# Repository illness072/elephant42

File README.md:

# elephant42 (🐘42)

## plates

|||
|--|--|
|dxf data in plates/|sandwitch mount with 6.5mm spacer|

## pcb

dependency on

  - https://github.com/foostan/kbd/tree/master/kicad-footprints/kbd.pretty

## cases

currently, not compatible with some switches.

## assembly

- [Build Guide (Japanese)](docs/build-guide.md)
- [Build Guide (English)](docs/build-guide-english.md)

## license?

Beerware!!

Come drink beer in Tokyo with me!! 🍺🍺🍺

## poor english?

Sorry, it's Google Translate.

# A small favor.

Could you generate a Gerber file from the origin/footprint branch and actually manufacture the PCB? 
We have implemented a fix for the footprint library link error and KiCAD6 support, but we have not yet been able to manufacture a PCB and test that it really works.
I would be most grateful if you could actually manufacture the PCB based on the footprint branch, check that it works, and report the results to me via Issue in this repository, my twitter, etc.
Thanks in advance.

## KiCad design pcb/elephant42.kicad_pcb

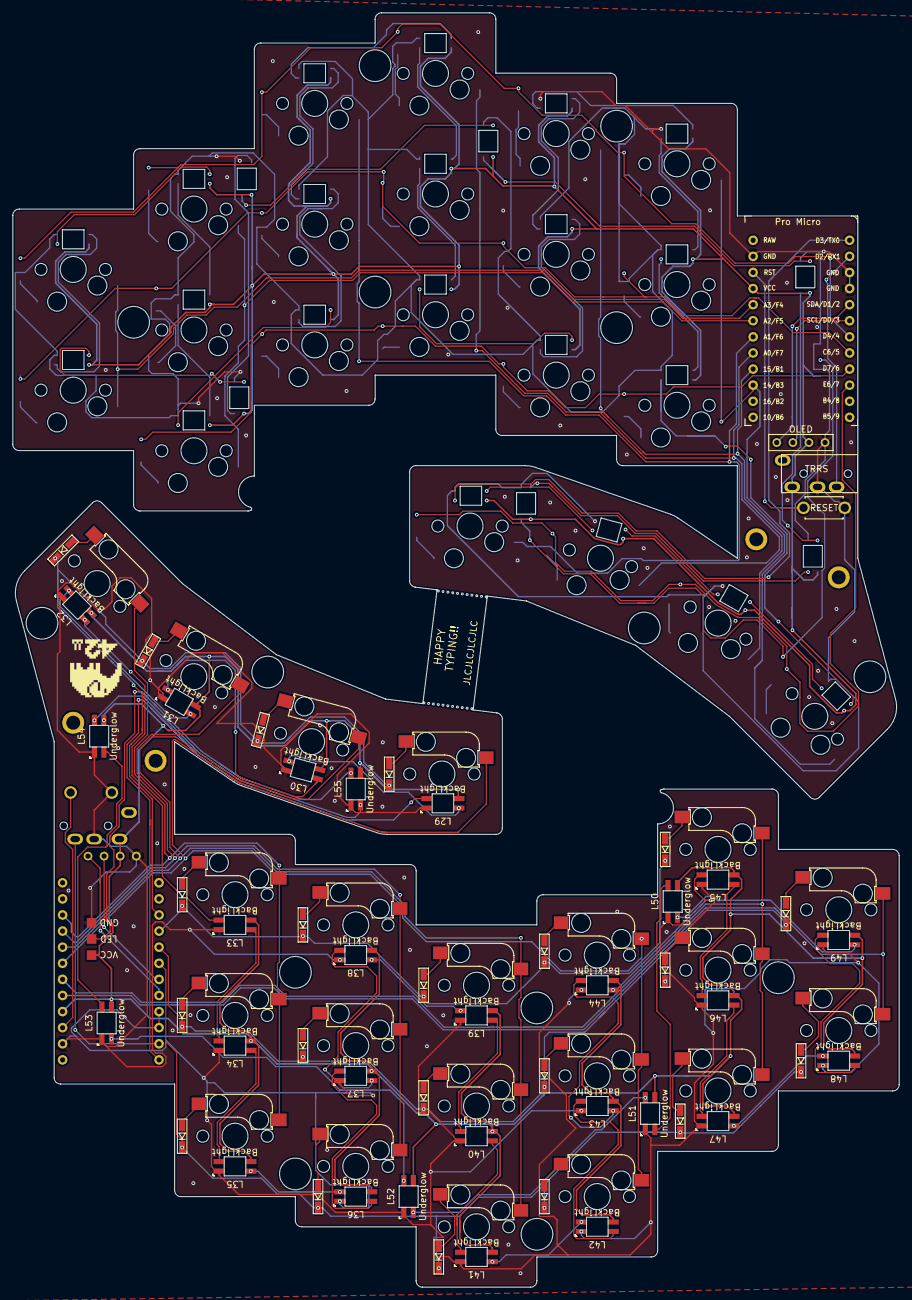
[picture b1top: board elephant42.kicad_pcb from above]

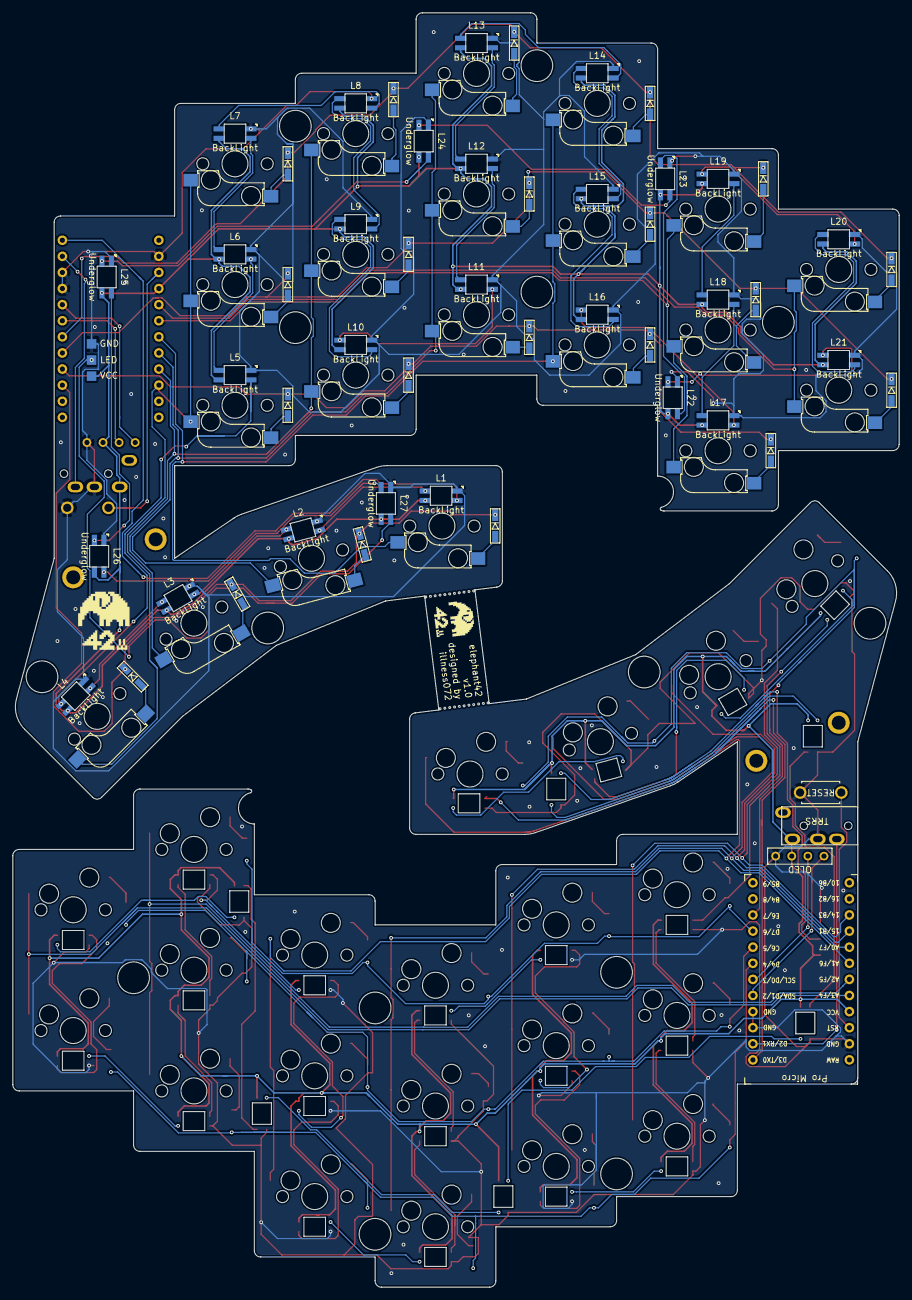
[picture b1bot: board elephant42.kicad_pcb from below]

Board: 2 copper layers, 139.8 x 201.0 mm, 152 parts (74 on the bottom side), 128 nets.

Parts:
D1, D2, D3, D4, D5, D6, D7, D8, D9, D10, D11, D12, D13, D14, D15, D16, D17, D18, D19, D20, D21, D22, D23, D24, D25, D26, D27, D28, D29, D30, D31, D32, D33, D34, D35, D36, D37, D38, D39, D40, D41, D42: D; D3_SMD_v2
J1, J3: MJ-4PP-9; MJ-4PP-9_1side
J4, J4#2, J4#3, J4#4: Conn_01x01; M2hole
L1, L2, L3, L4, L5, L6, L7, L8, L9, L10, L11, L12, L13, L14, L15, L16, L17, L18, L19, L20, L21, L29, L30, L31, L32, L33, L34, L35, L36, L37, L38, L39, L40, L41, L42, L43, L44, L45, L46, L47, L48, L49: YS-SK6812mini-E; YS-SK6812MINI-E
L22, L23, L24, L25, L26, L27, L50, L51, L52, L53, L54, L55: YS-SK6812mini-E; YS-SK6812MINI-E-underglow
L28, L56: LED; StripLED_1side
OL1, OL2: OLED; OLED_1side
RESET_SW1, RESET_SW2: SW_PUSH; ResetSW_1side
SW1, SW2, SW3, SW4, SW5, SW6, SW7, SW8, SW9, SW10, SW11, SW12, SW13, SW14, SW15, SW16, SW17, SW18, SW19, SW20, SW21, SW22, SW23, SW24, SW25, SW26, SW27, SW28, SW29, SW30, SW31, SW32, SW33, SW34, SW35, SW36, SW37, SW38, SW39, SW40, SW41, SW42: SW_PUSH; CherryMX_Hotswap
U1, U2: ProMicro; ProMicro_v3

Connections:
GND: J1.C, J3.C, L1.3, L2.3, L3.3, L4.3, L5.3, L6.3, L7.3, L8.3, L9.3, L10.3, L11.3, L12.3, L13.3, L14.3, L15.3, L16.3, L17.3, L18.3, L19.3, L20.3, L21.3, L22.3, L23.3, L24.3, L25.3, L26.3, L27.3, L28.3, L29.3, L30.3, L31.3, L32.3, L33.3, L34.3, L35.3, L36.3, L37.3, L38.3, L39.3, L40.3, L41.3, L42.3, L43.3, L44.3, L45.3, L46.3, L47.3, L48.3, L49.3, L50.3, L51.3, L52.3, L53.3, L54.3, L55.3, L56.3, OL1.4, OL2.4, RESET_SW1.2, RESET_SW2.2, U1.3, U1.4, U1.23, U2.3, U2.4, U2.23
unnamed: D1.2, SW1.2
unnamed: D2.2, SW2.2
unnamed: D3.2, SW3.2
unnamed: D4.2, SW4.2
unnamed: D5.2, SW5.2
unnamed: D6.2, SW6.2
unnamed: D7.2, SW7.2
unnamed: D8.2, SW8.2
unnamed: D9.2, SW9.2
unnamed: D10.2, SW10.2
unnamed: D11.2, SW11.2
unnamed: D12.2, SW12.2
unnamed: D13.2, SW13.2
unnamed: D14.2, SW14.2
unnamed: D15.2, SW15.2
unnamed: D16.2, SW16.2
unnamed: D17.2, SW17.2
unnamed: D18.2, SW18.2
unnamed: D19.2, SW19.2
unnamed: D20.2, SW20.2
unnamed: D21.2, SW21.2
unnamed: D22.2, SW22.2
unnamed: D23.2, SW23.2
unnamed: D24.2, SW24.2
unnamed: D25.2, SW25.2
unnamed: D26.2, SW26.2
unnamed: D27.2, SW27.2
unnamed: D28.2, SW28.2
unnamed: D29.2, SW29.2
unnamed: D30.2, SW30.2
unnamed: D31.2, SW31.2
unnamed: D32.2, SW32.2
unnamed: D33.2, SW33.2
unnamed: D34.2, SW34.2
unnamed: D35.2, SW35.2
unnamed: D36.2, SW36.2
unnamed: D37.2, SW37.2
unnamed: D38.2, SW38.2
unnamed: D39.2, SW39.2
unnamed: D40.2, SW40.2
unnamed: D41.2, SW41.2
unnamed: D42.2, SW42.2
unnamed: L1.2, L2.4
unnamed: L2.2, L3.4
unnamed: L3.2, L4.4
unnamed: L4.2, L5.4
unnamed: L5.2, L6.4
unnamed: L6.2, L7.4
unnamed: L7.2, L8.4
unnamed: L8.2, L9.4
unnamed: L10.2, L11.4
unnamed: L9.2, L10.4
unnamed: L11.2, L12.4
unnamed: L12.2, L13.4
unnamed: L13.2, L14.4
unnamed: L14.2, L15.4
unnamed: L15.2, L16.4
unnamed: L16.2, L17.4
unnamed: L17.2, L18.4
unnamed: L18.2, L19.4
unnamed: L19.2, L20.4
unnamed: L20.2, L21.4
unnamed: L21.2, L22.4
unnamed: L22.2, L23.4
unnamed: L23.2, L24.4
unnamed: L24.2, L25.4
unnamed: L25.2, L26.4
unnamed: L26.2, L27.4
unnamed: L27.2, L28.2
unnamed: L29.2, L30.4
unnamed: L30.2, L31.4
unnamed: L31.2, L32.4
unnamed: L32.2, L33.4
unnamed: L33.2, L34.4
unnamed: L34.2, L35.4
unnamed: L35.2, L36.4
unnamed: L36.2, L37.4
unnamed: L37.2, L38.4
unnamed: L38.2, L39.4
unnamed: L39.2, L40.4
unnamed: L40.2, L41.4
unnamed: L41.2, L42.4
unnamed: L42.2, L43.4
unnamed: L43.2, L44.4
unnamed: L44.2, L45.4
unnamed: L45.2, L46.4
unnamed: L46.2, L47.4
unnamed: L47.2, L48.4
unnamed: L48.2, L49.4
unnamed: L49.2, L50.4
unnamed: L50.2, L51.4
unnamed: L51.2, L52.4
unnamed: L52.2, L53.4
unnamed: L53.2, L54.4
unnamed: L54.2, L55.4
unnamed: L55.2, L56.2
VCC: J1.D, J3.D, L1.1, L2.1, L3.1, L4.1, L5.1, L6.1, L7.1, L8.1, L9.1, L10.1, L11.1, L12.1, L13.1, L14.1, L15.1, L16.1, L17.1, L18.1, L19.1, L20.1, L21.1, L22.1, L23.1, L24.1, L25.1, L26.1, L27.1, L28.1, L29.1, L30.1, L31.1, L32.1, L33.1, L34.1, L35.1, L36.1, L37.1, L38.1, L39.1, L40.1, L41.1, L42.1, L43.1, L44.1, L45.1, L46.1, L47.1, L48.1, L49.1, L50.1, L51.1, L52.1, L53.1, L54.1, L55.1, L56.1, OL1.3, OL2.3, U1.21, U2.21
col0: SW1.1, SW7.1, U1.20
col1: SW2.1, SW8.1, SW13.1, U1.19
col2: SW3.1, SW9.1, SW14.1, SW18.1, U1.18
col3: SW4.1, SW10.1, SW15.1, SW19.1, U1.17
col4: SW5.1, SW11.1, SW16.1, SW20.1, U1.16
col5: SW6.1, SW12.1, SW17.1, SW21.1, U1.15
col6: SW27.1, SW33.1, U2.20
col7: SW26.1, SW32.1, SW38.1, U2.19
col8: SW25.1, SW31.1, SW37.1, SW42.1, U2.18
col9: SW24.1, SW30.1, SW36.1, SW41.1, U2.17
col10: SW23.1, SW29.1, SW35.1, SW40.1, U2.16
col11: SW22.1, SW28.1, SW34.1, SW39.1, U2.15
data_l: J1.B, U1.2
data_r: J3.B, U2.2
led_l: L1.4, U1.1
led_r: L29.4, U2.1
reset_l: RESET_SW1.1, U1.22
reset_r: RESET_SW2.1, U2.22
row0: D1.1, D2.1, D3.1, D4.1, D5.1, D6.1, U1.7
row1: D7.1, D8.1, D9.1, D10.1, D11.1, D12.1, U1.8
row2: D13.1, D14.1, D15.1, D16.1, D17.1, U1.9
row3: D18.1, D19.1, D20.1, D21.1, U1.10
row4: D22.1, D23.1, D24.1, D25.1, D26.1, D27.1, U2.7
row5: D28.1, D29.1, D30.1, D31.1, D32.1, D33.1, U2.8
row6: D34.1, D35.1, D36.1, D37.1, D38.1, U2.9
row7: D39.1, D40.1, D41.1, D42.1, U2.10
scl_l: OL2.2, U1.6
scl_r: OL1.2, U2.6
sda_l: OL2.1, U1.5
sda_r: OL1.1, U2.5

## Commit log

2019-12-01 Create LICENSE
2019-12-01 added plate data
2019-12-01 added descrpiption
2019-12-01 added PCB data
2019-12-01 added case data.
2019-12-01 add picture
2019-12-20 add LED
2019-12-29 jlcpcb
2020-01-09 small fix
2020-01-15 update gitignore
2020-01-15 update plates
2020-01-15 update cases
2020-01-15 add pictures
2020-01-16 added Keyboard Layout Editor JSON
2020-01-18 add item-list
2020-01-19 setup guide
2020-01-20 update build-guide: split PCB, LED
2020-01-20 update build-guide: small fix
2020-01-20 update build-guide: solder complete
2020-01-20 update build-guide: assemble complete
2020-01-20 resize images
2020-01-20 thank you nrtkbb-san!
2020-01-25 move images
2020-01-26 rename dir
2020-01-26 Set theme jekyll-theme-slate
2020-01-27 update build-guide: enable OLED
2020-01-27 update buildguide: update toc
2020-01-28 add mysterious document
2020-05-27 fix th
2020-07-04 v1 pcb
2020-07-06 add file
2020-07-06 add cases
2020-07-06 update build-guide
2020-07-24 add via files
2020-07-27 update docs
2020-12-26 add v2 case
2021-01-15 add youtube link
2021-01-15 update toc
2021-03-08 Adds a google translated version of build guide
2021-03-08 Cleanse up some of the mess google added in translation
2021-03-08 Cleans up some more formatting issues from google translate
2021-03-08 Resolves some more list formatting issues
2021-03-08 Adds some more list formatting in hopes of better github compatibility
2021-03-08 Fixed more formatting issues caused by my search/replace methods
2021-03-08 Fixes a couple more little things
2021-03-08 More formatting
2021-10-24 move via files to firmware-repository
2021-12-09 archive footprint
2021-12-09 archive lib
2021-12-10 updat sch
2022-04-25 kicad6
2022-05-14 Add files via upload
    Add plate data for Yusha-Kobo laser cut
2022-05-15 Fix plate data
2022-05-16 Add files via upload (#10)
    * Add files via upload
    Add plate data for Yusha-Kobo laser cut
    * Fix plate data
2022-05-19 README: Fixes link to kbd.pretty
2022-05-19 README: Fixes link to kbd.pretty (#11)
